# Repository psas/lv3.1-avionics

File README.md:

# lv3.1-avionics
Avionics for the LV3.1 rocket

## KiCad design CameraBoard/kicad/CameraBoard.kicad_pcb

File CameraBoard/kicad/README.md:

---
title: "**LV3 Camera Board**"
subtitle: |
  **Fabrication and Assembly Information**\
  For build TIME-STAMP
fontsize: 10pt
geometry:
  - margin=0.5in
toc: true
toc-depth: 2
colorlinks: true
urlcolor: blue

\newpage

# About this Board

## Board Description

This board runs the 9 cameras for the 360 view camera setup on LV3.x. It takes 19V to charge the 4S battery pack,
and only runs the cameras when rocketready is asserted.

## Documentation Links

- Git repository: <https://github.com/psas/lv3.1-avionics>
- **TODO:** Design Notes + Design Review Notes

## Documentation Files

| Filename                        | Notes                                    |
| ------------------------------- | ---------------------------------------- |
| README.pdf                      | This README file                         |
| flatsat-breakout-outline.dxf        | Board outline (with holes) in DXF format |
| flatsat-breakout-pcba.step          | 3D model of PCBA (with components)       |
| flatsat-breakout-render-bot.jpg     | Render of the top of the 3D model        |
| flatsat-breakout-render-bot.jpg     | Render of the bottom of the 3D model     |
| flatsat-breakout-schematic.pdf      | PDF of board schematics                  |

## Contact Information

- Website: <https://www.pdxaerospace.org/>
- Email: <aerospace@pdx.edu>
- Instagram: @pdxaerospace

## Board Renders

{width=50%}
{width=50%}

\newpage

# Printed Circuit Board (PCB) Fabrication Information

## Board Info

- 2 layer board
- Bounding box is 101.6000 x 76.2000 mm
- Board thickness is 1.59 mm (0.063 inch)

## Board Requirements

- Design Rules
    - Minimum Trace / Space design rulea: 0.1524 mm (6.0 mil) / 0.1524 mm (6.0 mil)
    - Outer dimension router tolerance: +/- 0.254 mm (10.0 mil)
    - Hole placement tolerance: +/- 0.075 mm (3.0 mil)
- Drills
   - Drill Positional Tolerance: 0.051 mm (2.0 mil)
   - Drill Size tolerance: +/- 0.064 mm (2.5 mil)
- Plated/Un-plated holes
  - There are no un-plated (NPT) holes
  - There are 96 plated through (PTH) holes
  - PTH minimum diameter: 0.254 mm (10 mil)
  - PTH minimum annulus: 0.102 mm (4 mil) radius
- Outline/Routing
  - No requirements.
- Slots
  - There are no slots.
- Cutouts
  - There are no cutouts
- There are 3 fiducials on the top layer.
- Panel tabs ("mouse bites")
   - Card edges must be smooth; no mouse bites or other intrusions into the card outline.
   - If external mouse bites are required, minimize and customer will remove by hand before assembly.
- If not otherwise specified, build to IPC 6012 Class 2 or better.

## Materials

- No requirements for materials.
- Copper Surface treatment should be ENIG, althogh immersion Silver is acceptable.
- White silkscreen on top and bottom surface
- Taiyo PSR-4000 or equivalent soldermask on top and bottom, no requirements for color.

## Stack Up

- Any FR4 like material is acceptable.
- 1 oz Copper on top and bottom layers
- 1.6 mm thick when done (1/16 inch)

## Array / Panel Information

- Coordinate with Contract Manufacturer (CM) for optimal size of this panel.
- If no feedback from CM, then produce single boards (no panel).

## Fabrication Files

### IPC-2581 File

| Filename                 | Notes                                   |
| ------------------------ | --------------------------------------- |
| PROJECT-NAME-ipc2581.xml | IPC-2581 board information file         |

### Legacy PCB Files

| Filename                      | Notes                                         |
| ------------------------------| --------------------------------------------- |
| PROJECT-NAME-Edge_Cuts.gbr    | RS274X file for the dimension (outline) layer |
| PROJECT-NAME-F_Silkscreen.gbr | RS274X file for the top silkscreen            |
| PROJECT-NAME-F_Mask.gbr       | RS274X file for the top soldermask            |
| PROJECT-NAME-F_Cu.gbr         | RS274X file for the top copper layer          |
| PROJECT-NAME-In1_Cu.gbr       | RS274X file for the layer 2 copper            |
| PROJECT-NAME-In2_Cu.gbr       | RS274X file for the layer 3 copper            |
| PROJECT-NAME-B_Cu.gbr         | RS274X file for the bottom copper layer       |
| PROJECT-NAME-B_Mask.gbr       | RS274X file for the bottom soldermask         |
| PROJECT-NAME-B_Silkscreen.gbr | RS274X file for the bottom silkscreen         |
| PROJECT-NAME-NPTH.drl         | Excellon file for non-plated through holes    |
| PROJECT-NAME-PTH.drl          | Excellon file for plated through holes        | 

\newpage

# Printed Circuit Board Assembly (PCBA) Information

## Assembly Info

- All components are on the top side of the board.
- Mixed SMT and TH components.

## Assembly Requirements

- Assemble to IPC Class 2 or better
- Solder paste can be ROHS or leaded.
- No clean, or Aqueous flux and wash, can be used.
- No conformal coating.

## Component Specific Assembly Information

- None

## Assembly Files

### IPC-2581 File

| Filename                 | Notes                           |
| ------------------------ | ------------------------------- |
| PROJECT-NAME-ipc2581.xml | IPC-2581 board information file |

### Bill of Materials (BOM)

| Filename             | Description                            |
| -------------------- | -------------------------------------- |
| PROJECT-NAME-bom.csv | BOM in Comma Separated Variable format |

### Solder Paste Stencils

| Filename                 | Notes                                            |
| ------------------------ | ------------------------------------------------ |
| PROJECT-NAME-B_Paste.gbr | RS274X file for top/front solder paste stencil   |
| PROJECT-NAME-F_Paste.gbr | RS274X file for bottom/back solder paste stencil |

### Mounting/Placement Location

| Filename            | Description                                 |
| ------------------- | ------------------------------------------- |
| PROJECT-NAME-3u.pos | Pick and place locations for components     |

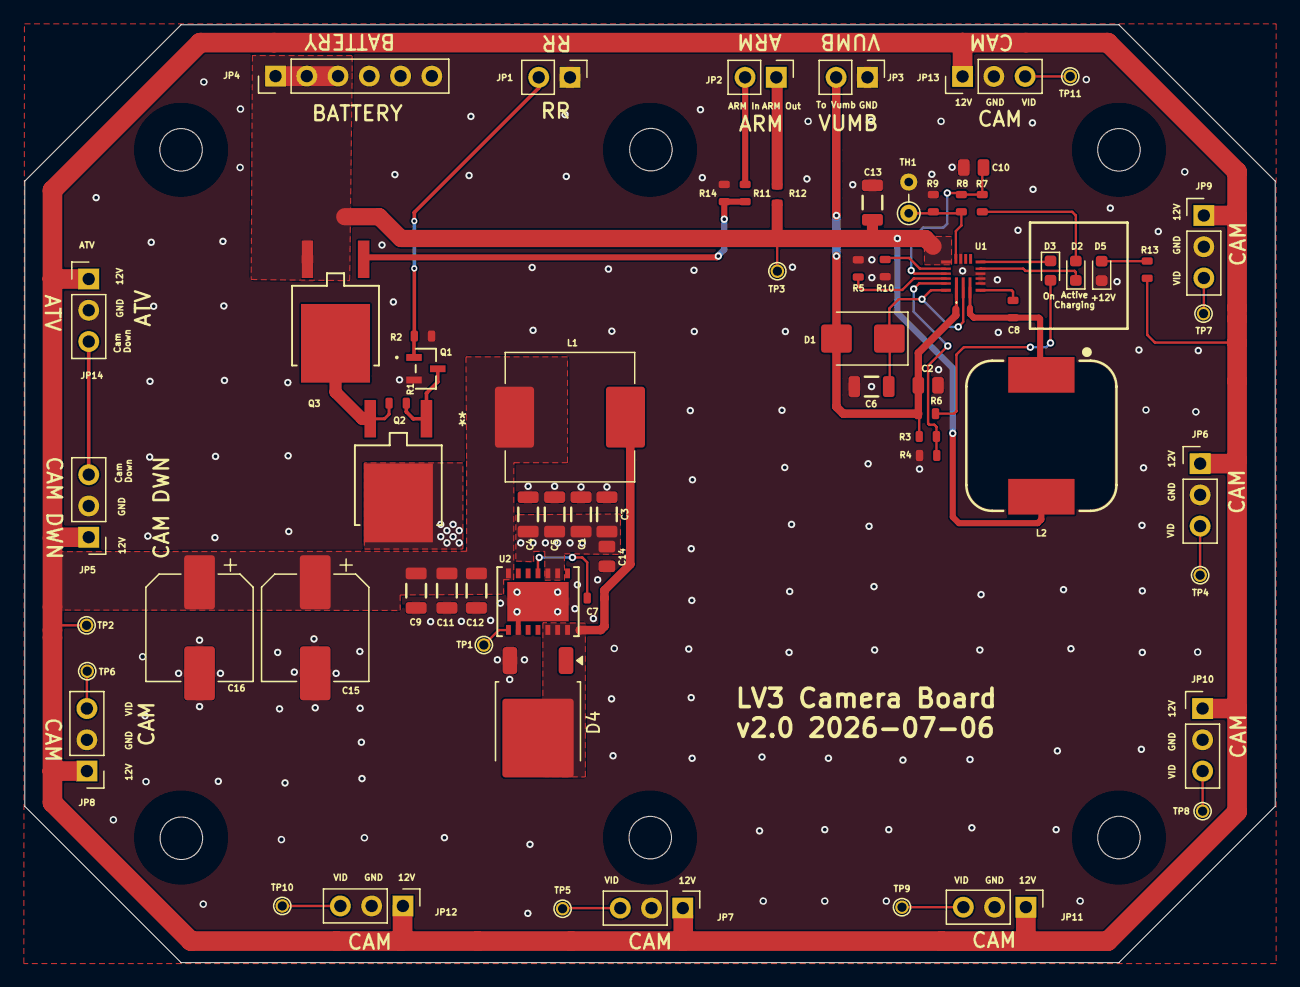
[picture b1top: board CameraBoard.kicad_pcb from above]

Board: 2 copper layers, 101.6 x 76.2 mm, 68 parts (0 on the bottom side), 36 nets.

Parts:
C1, C3, C4, C5, C9, C11, C12, C13: 10u; 1206-C
C2, C10, C14: 1u; 0805-C-NOSILK
C6: 2.2u; 1206-C
C7: 10n; 0603-C-NOSILK
C8: 100n; 0603-C-NOSILK
C15, C16: 100u; CP_Elec_8x10.5
D1: B240; D_SMB
D2, D3: AMB; LED_0603_1608Metric
D4: MBRD835; TO-252-2
D5: GRN; LED_0603_1608Metric
JP1, JP2, JP3: PinHeader_1x02_P2.54mm_Vertical
JP4: PINHD-1X6; PinHeader_1x06_P2.54mm_Vertical
JP5, JP6, JP7, JP8, JP9, JP10, JP11, JP12, JP13, JP14: PINHD-1X3; PinHeader_1x03_P2.54mm_Vertical
L1: 22u; L_Vishay_IHLP-4040
L2: 10u; WE-PD_1260
Q1: DMG3404L-7; DMG3404L_DIO
Q2, Q3: AOD4185; TO252_AOS-M
R1, R2, R4, R6, R13: 10k; 0603-C-NOSILK
R3: 133k; 0603-C-NOSILK
R5: 33k; 0603-C-NOSILK
R7: 2k; 0603-C-NOSILK
R8: 2.26k; 0603-C-NOSILK
R9: 6.98k; 0603-C-NOSILK
R10: 38.3k; 0603-C-NOSILK
R11, R12: 1k; 0603-C-NOSILK
R14: 150k; 0603-C-NOSILK
TH1: 10k; R_Axial_DIN0204_L3.6mm_D1.6mm_P2.54mm_Vertical
TP1, TP2, TP3, TP4, TP5, TP6, TP7, TP8, TP9, TP10, TP11: Test-Point; TestPoint-0.75mm-th
U1: MP2659GQ-0000-Z; MP2659GQ0000Z
U2: LM2678SD-ADJ/NOPB; SRC14A

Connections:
+12V: C9.1, C11.1, C12.1, C15.1, C16.1, JP5.1, JP6.1, JP7.1, JP8.1, JP9.1, JP10.1, JP11.1, JP12.1, JP13.1, JP14.1, L1.2, R13.2, TP2.1 (1_1), U2.7 (FB)
/ARM-IN: JP2.2, R11.1
/ARM-OUT: JP2.1, R12.1
/BATT+: C13.1, JP4.1, JP4.2, JP4.3, L2.2, Q3.3 (S), R12.2, TP3.1 (1_1), U1.14 (BATT)
/CAM_DOWN: JP5.3, JP14.3
/VUMB: C2.1, D1.2 (A), JP3.2, R3.2, R6.1, U1.1 (IN)
GND: C1.2, C2.2, C3.2, C4.2, C5.2, C6.1, C9.2, C10.2, C11.2, C12.2, C13.2, C14.2, C15.2, C16.2, D4.3 (A), D5.1 (K), JP1.1, JP3.1, JP4.4, JP4.5, JP4.6, JP5.2, JP6.2, JP7.2, JP8.2, JP9.2, JP10.2, JP11.2, JP12.2, JP13.2, JP14.2, Q1.2 (S), R2.2, R4.1, R5.1, R9.2, R10.2, R14.2, TH1.2, U1.5 (PGND), U1.6 (PGND), U1.7 (PGND), U1.12 (AGND), U2.9 (GND), U2.15 (GND)
unnamed: C6.2, D1.1 (K), U1.2 (PMID), U1.19 (PMID_S)
unnamed: D2.2 (A), R6.2
unnamed: D2.1 (K), U1.9 (~ACOK)
unnamed: D3.2 (A), R7.2
unnamed: D3.1 (K), U1.8 (~STAT)
unnamed: C7.1, D4.2 (K), L1.1, U2.12 (SW), U2.13 (SW), U2.14 (SW)
unnamed: D5.2 (A), R13.1
unnamed: JP1.2, Q1.1 (G), R2.1
unnamed: JP6.3, TP4.1 (1_1)
unnamed: JP7.3, TP5.1 (1_1)
unnamed: JP8.3, TP6.1 (1_1)
unnamed: JP9.3, TP7.1 (1_1)
unnamed: JP10.3, TP8.1 (1_1)
unnamed: JP11.3, TP9.1 (1_1)
unnamed: JP12.3, TP10.1 (1_1)
unnamed: JP13.3, TP11.1 (1_1)
unnamed: Q1.3 (D), Q2.1 (G), R1.2
unnamed: C1.1, C3.1, C4.1, C5.1, C14.1, Q2.2 (D), U2.2 (Vin), U2.3 (Vin)
unnamed: Q3.1 (G), R11.2, R14.1
unnamed: C8.1, U1.4 (BST)
unnamed: R5.2, U1.17 (ILIM)
unnamed: R10.1, U1.15 (ISET)
unnamed: R8.2, R9.1, TH1.1, U1.13 (NTC)
unnamed: C8.2, L2.1, U1.3 (SW)
unnamed: R3.1, R4.2, U1.18 (VDPM)
unnamed: C7.2, U2.4 (BOOST)
unnamed: TP1.1 (1_1), U2.8 (ON)
VBATT: Q2.3 (S), Q3.2 (D), R1.1
VCC: C10.1, R7.1, R8.1, U1.16 (VCC)

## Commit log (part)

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2020-02-05 added file
2020-04-22 adding first design review notes
2020-04-23 power schematic for board
2020-04-23 first draft of schematic complete
2020-04-24 layed out board before routing
2020-04-24 finished board layout before routing
2020-04-24 completed routing of board rev 1.0
2020-04-28 new image
2020-04-29 added all the suggestions from first design review
2020-04-29 moved text around, and added new .jpg
2020-07-07 added BOM
2020-07-20 Minor erc and drc cleanup, ground plane cleanup, nothing major.
2020-10-05 Added molex connectors
2023-08-20 Added KiCAD 7 import of CameraBoard. Updated .gitignore file, too.
2025-06-24 Updated KiCAD EAGLE import to latest KiCAD 9.0.2.
2025-07-02 Added wiring diagram; avionics module complete!
2025-07-02 Added connector notes
2025-07-02 Add note on extra wire length
2025-07-16 Added umbilical ring connections
2025-07-16 Minor polishing
2025-07-30 Added another connector on umbilical cord
2025-08-02 Changed pulldown to 150k and added note about flipped connector.
2025-08-03 Cleaned up second page - fixed optoisolator symbols, added notes about levels and times, and cleaned up alot. Put in notes about mod wires.
2025-08-04 Make schematic better, mostly cleaning up EAGLE import errors
2026-01-28 Added umbilical cable adapter with labels
2026-03-12 Minor updates to PCB
2026-04-26 replaced the timer logic for a d flip flop
